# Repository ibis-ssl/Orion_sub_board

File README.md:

# Orion_sub_board
Orionのサブ基板
こちらに統合 → https://github.com/ChikuwaRobo/KiCAD_Projects.git

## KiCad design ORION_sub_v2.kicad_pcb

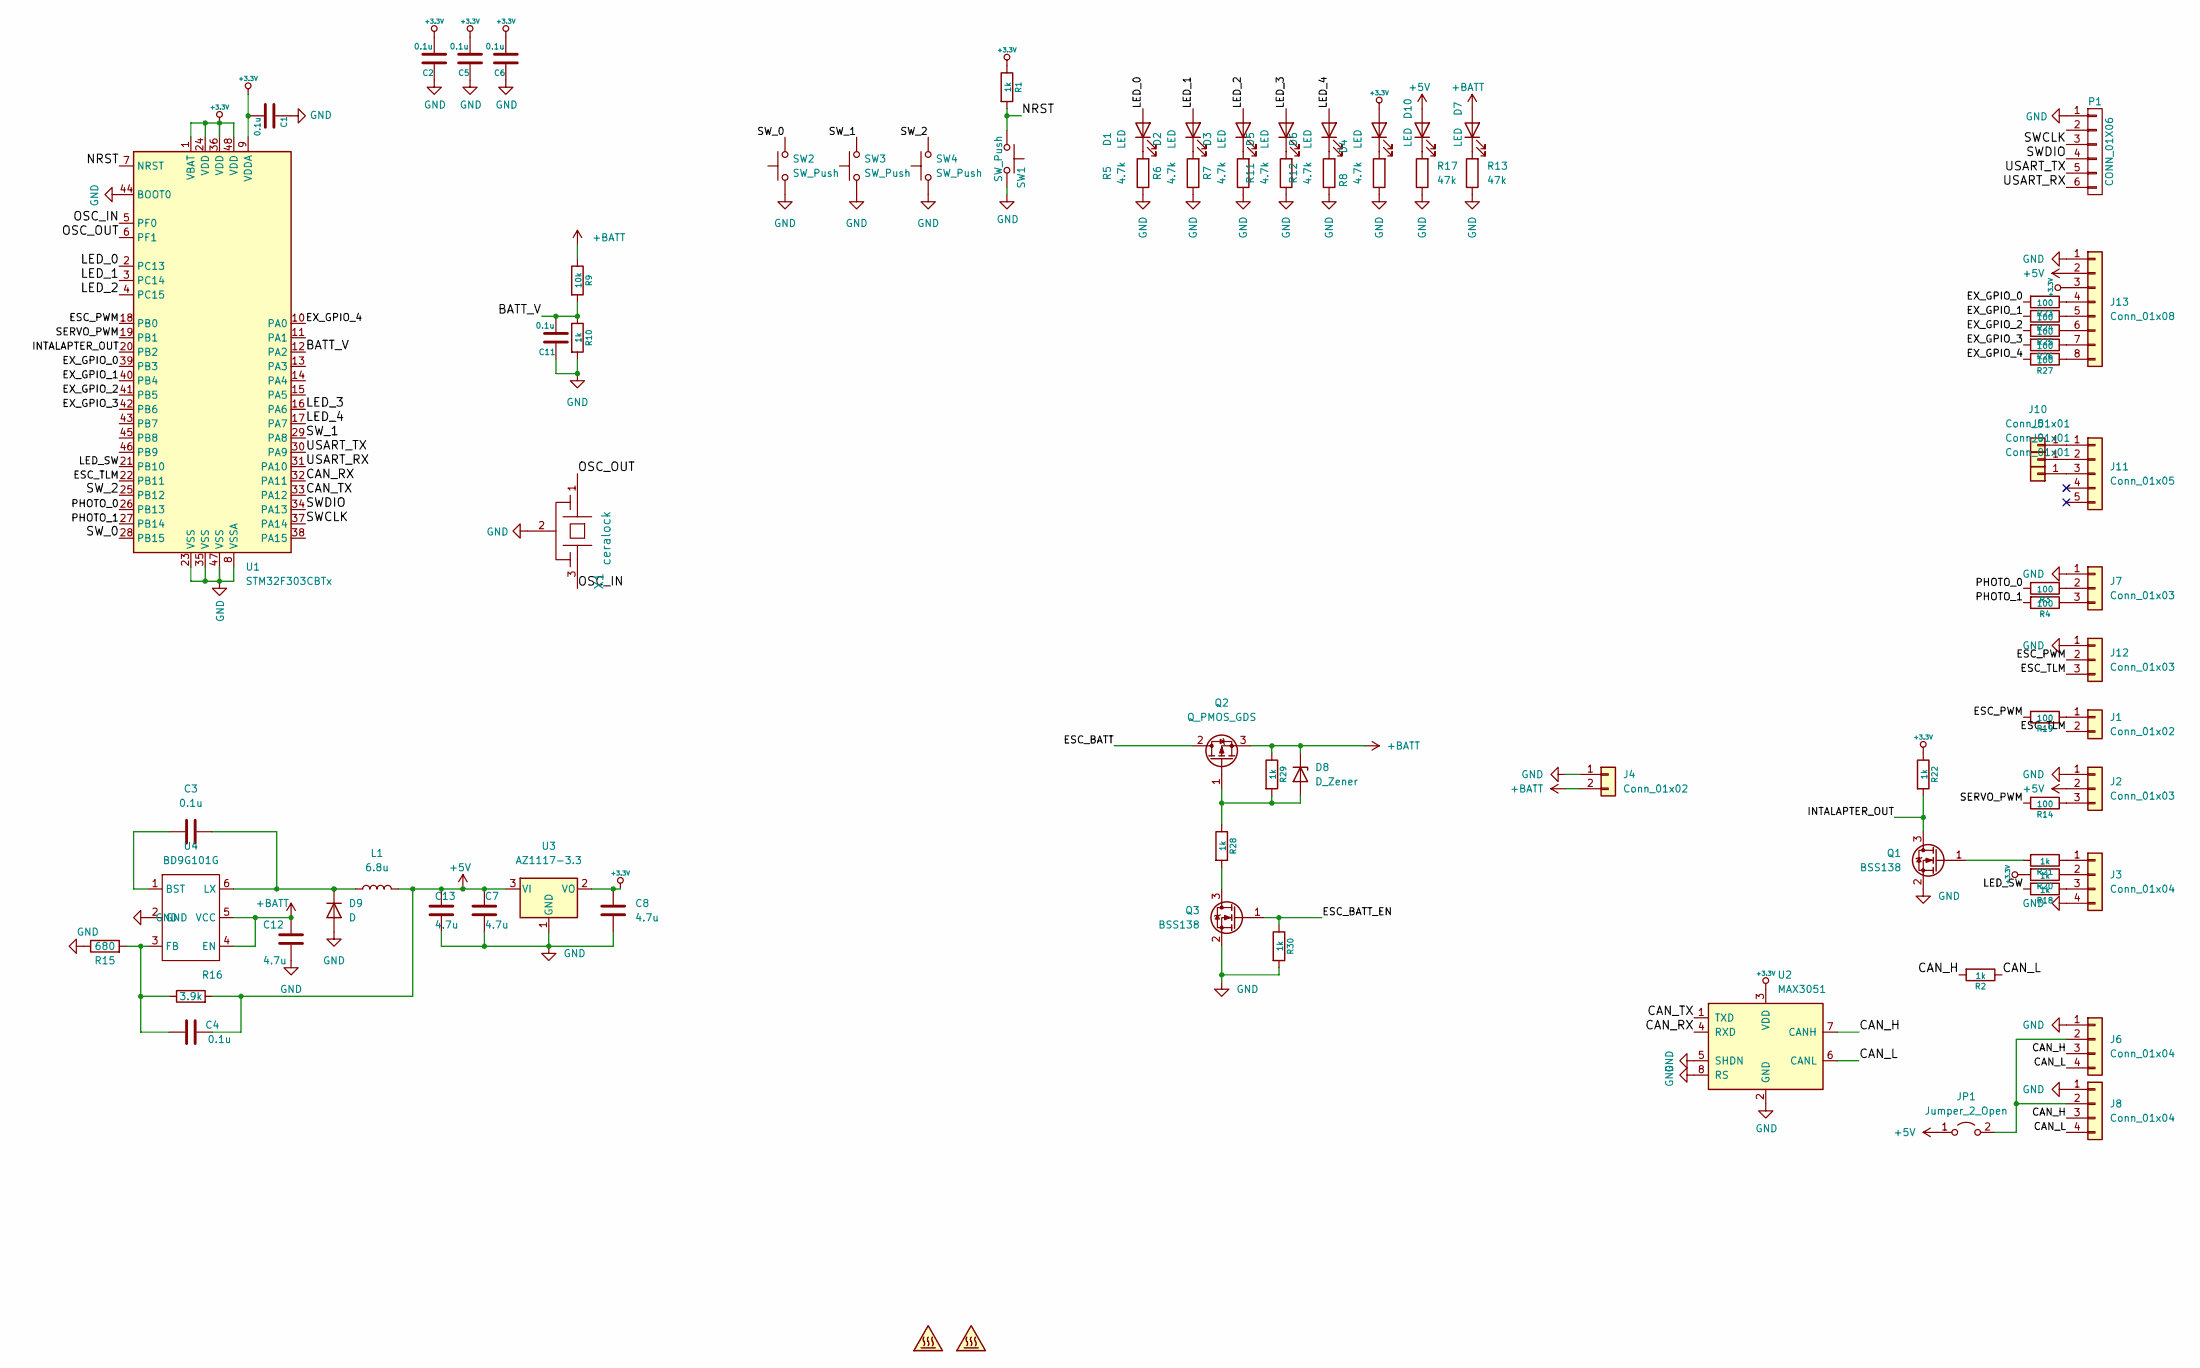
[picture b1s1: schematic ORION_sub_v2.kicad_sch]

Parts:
C1, C2, C5, C6, C11: 0.1u; C_0603_1608Metric
C3, C4: 0.1u; C_0402_1005Metric
C7, C8, C12, C13: 4.7u; C_1206_3216Metric
D1, D2, D3, D4, D5, D6, D7, D10: LED; LED_0603_1608Metric
D8: D_Zener; D_0805_2012Metric
D9: D; D_PowerDI-123
J1: Conn_01x02; Hirose_DF13-02P-1.25DSA_1x02_P1.25mm_Vertical
J2: Conn_01x03; JST_PH_S3B-PH-K_1x03_P2.00mm_Horizontal
J3, J6, J8: Conn_01x04; Hirose_DF13-04P-1.25DSA_1x04_P1.25mm_Vertical
J4: Conn_01x02; AMASS_XT30PW-M_1x02_P2.50mm_Horizontal
J5, J9, J10: Conn_01x01; WireSoldingPad_PowerTH
J7: Conn_01x03; Hirose_DF13-03P-1.25DSA_1x03_P1.25mm_Vertical
J11: Conn_01x05; 2053380003
J12: Conn_01x03; PinSocket_1x03_P2.54mm_Vertical
J13: Conn_01x08; Hirose_DF13-08P-1.25DSA_1x08_P1.25mm_Vertical
JP1: Jumper_2_Open; SolderJumper-2_P1.3mm_Open_RoundedPad1.0x1.5mm
L1: 6.8u; L_Taiyo-Yuden_NR-50xx
LG1: SYM_Hot_Small; ibis_logo_10x8mm_mask
LG2: SYM_Hot_Small; ibis_logo_10x8mm_silk
P1: CONN_01X06; ZH_B6B-ZR
Q1, Q3: BSS138; SOT-23
Q2: Q_PMOS_GDS; TO-252-2
R1, R2, R10, R18, R20, R21, R22, R28, R29, R30: 1k; R_0603_1608Metric
R3, R4, R14, R19, R23, R24, R25, R26, R27: 100; R_0603_1608Metric
R5, R6, R7, R8, R11, R12: 4.7k; R_0603_1608Metric
R9: 10k; R_0603_1608Metric
R13, R17: 47k; R_0603_1608Metric
R15: 680; R_0603_1608Metric
R16: 3.9k; R_0603_1608Metric
SW1, SW2, SW3, SW4: SW_Push; SW_Push_1P1T_NO_CK_KMR2
U1: STM32F303CBTx; LQFP-48_7x7mm_P0.5mm
U2: MAX3051; SO-8_3.9x4.9mm_P1.27mm
U3: AZ1117-3.3; SOT-23
U4: BD9G101G; SOT-23-6
X1: ceralock; Resonator_SMD_Murata_CSTxExxV-3Pin_3.0x1.1mm

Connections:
+3.3V: C1.2, C2.2, C5.2, C6.2, C8.1, D4.2 (A), J13.3, R1.1, R20.2, R22.1, U1.1 (VBAT), U1.9 (VDDA), U1.24 (VDD), U1.36 (VDD), U1.48 (VDD), U2.3 (VDD), U3.2 (VO)
+5V: C4.1, C7.1, C13.1, D10.2 (A), J2.2, J13.2, JP1.1 (A), L1.2, R16.2, U3.3 (VI)
+BATT: C12.1, D7.2 (A), D8.1 (K), J4.2, Q2.3 (S), R9.1, R29.1, U4.4 (EN), U4.5 (VCC)
/BATT_V: C11.2, R9.2, R10.1, U1.12 (PA2)
/CAN_H: J6.3, J8.3, R2.2, U2.7 (CANH)
/CAN_L: J6.4, J8.4, R2.1, U2.6 (CANL)
/CAN_RX: U1.32 (PA11), U2.4 (RXD)
/CAN_TX: U1.33 (PA12), U2.1 (TXD)
/ESC_BATT: Q2.2 (D)
/ESC_BATT_EN: Q3.1 (G), R30.1
/ESC_PWM: J12.2, R19.2, U1.18 (PB0)
/ESC_TLM: J1.2, J12.3, U1.22 (PB11)
/EX_GPIO_0: R23.2, U1.39 (PB3)
/EX_GPIO_1: R24.2, U1.40 (PB4)
/EX_GPIO_2: R25.2, U1.41 (PB5)
/EX_GPIO_3: R26.2, U1.42 (PB6)
/EX_GPIO_4: R27.2, U1.10 (PA0)
/INTALAPTER_OUT: Q1.3 (D), R22.2, U1.20 (PB2)
/LED_0: D1.2 (A), U1.2 (PC13)
/LED_1: D2.2 (A), U1.3 (PC14)
/LED_2: D3.2 (A), U1.4 (PC15)
/LED_3: D5.2 (A), U1.16 (PA6)
/LED_4: D6.2 (A), U1.17 (PA7)
/LED_SW: R18.2, U1.21 (PB10)
/NRST: R1.2, SW1.1, U1.7 (NRST)
/OSC_IN: U1.5 (PF0), X1.3
/OSC_OUT: U1.6 (PF1), X1.1
/PHOTO_0: R3.2, U1.26 (PB13)
/PHOTO_1: R4.2, U1.27 (PB14)
/SERVO_PWM: R14.2, U1.19 (PB1)
/SWCLK: P1.3, U1.37 (PA14)
/SWDIO: P1.4, U1.34 (PA13)
/SW_0: SW2.2, U1.28 (PB15)
/SW_1: SW3.2, U1.29 (PA8)
/SW_2: SW4.2, U1.25 (PB12)
/USART_RX: P1.6, U1.31 (PA10)
/USART_TX: P1.5, U1.30 (PA9)
GND: C1.1, C2.1, C5.1, C6.1, C7.2, C8.2, C11.1, C12.2, C13.2, D9.2 (A), J2.1, J3.4, J4.1, J6.1, J7.1, J8.1, J12.1, J13.1, P1.1, Q1.2 (S), Q3.2 (S), R5.1, R6.1, R7.1, R8.1, R10.2, R11.1, R12.1, R13.1, R15.1, R17.1, R30.2, SW1.2, SW2.1, SW3.1, SW4.1, U1.8 (VSSA), U1.23 (VSS), U1.35 (VSS), U1.44 (BOOT0), U1.47 (VSS), U2.2 (GND), U2.5 (SHDN), U2.8 (RS), U3.1 (GND), U4.2 (GND), X1.2
unnamed: C3.1, D9.1 (K), L1.1, U4.6 (LX)
unnamed: C3.2, U4.1 (BST)
unnamed: C4.2, R15.2, R16.1, U4.3 (FB)
unnamed: D1.1 (K), R5.2
unnamed: D2.1 (K), R6.2
unnamed: D3.1 (K), R7.2
unnamed: D4.1 (K), R8.2
unnamed: D5.1 (K), R11.2
unnamed: D6.1 (K), R12.2
unnamed: D7.1 (K), R13.2
unnamed: D8.2 (A), Q2.1 (G), R28.1, R29.2
unnamed: D10.1 (K), R17.2
unnamed: J1.1, R19.1
unnamed: J2.3, R14.1
unnamed: J3.1, R21.1
unnamed: J3.2, R20.1
unnamed: J3.3, R18.1
unnamed: J6.2, J8.2, JP1.2 (B)
unnamed: J7.2, R3.1
unnamed: J7.3, R4.1
unnamed: J10.1, J11.1
unnamed: J5.1, J11.2
unnamed: J9.1, J11.3
unnamed: J13.4, R23.1
unnamed: J13.5, R24.1
unnamed: J13.6, R25.1
unnamed: J13.7, R26.1
unnamed: J13.8, R27.1
unnamed: Q1.1 (G), R21.2
unnamed: Q3.3 (D), R28.2

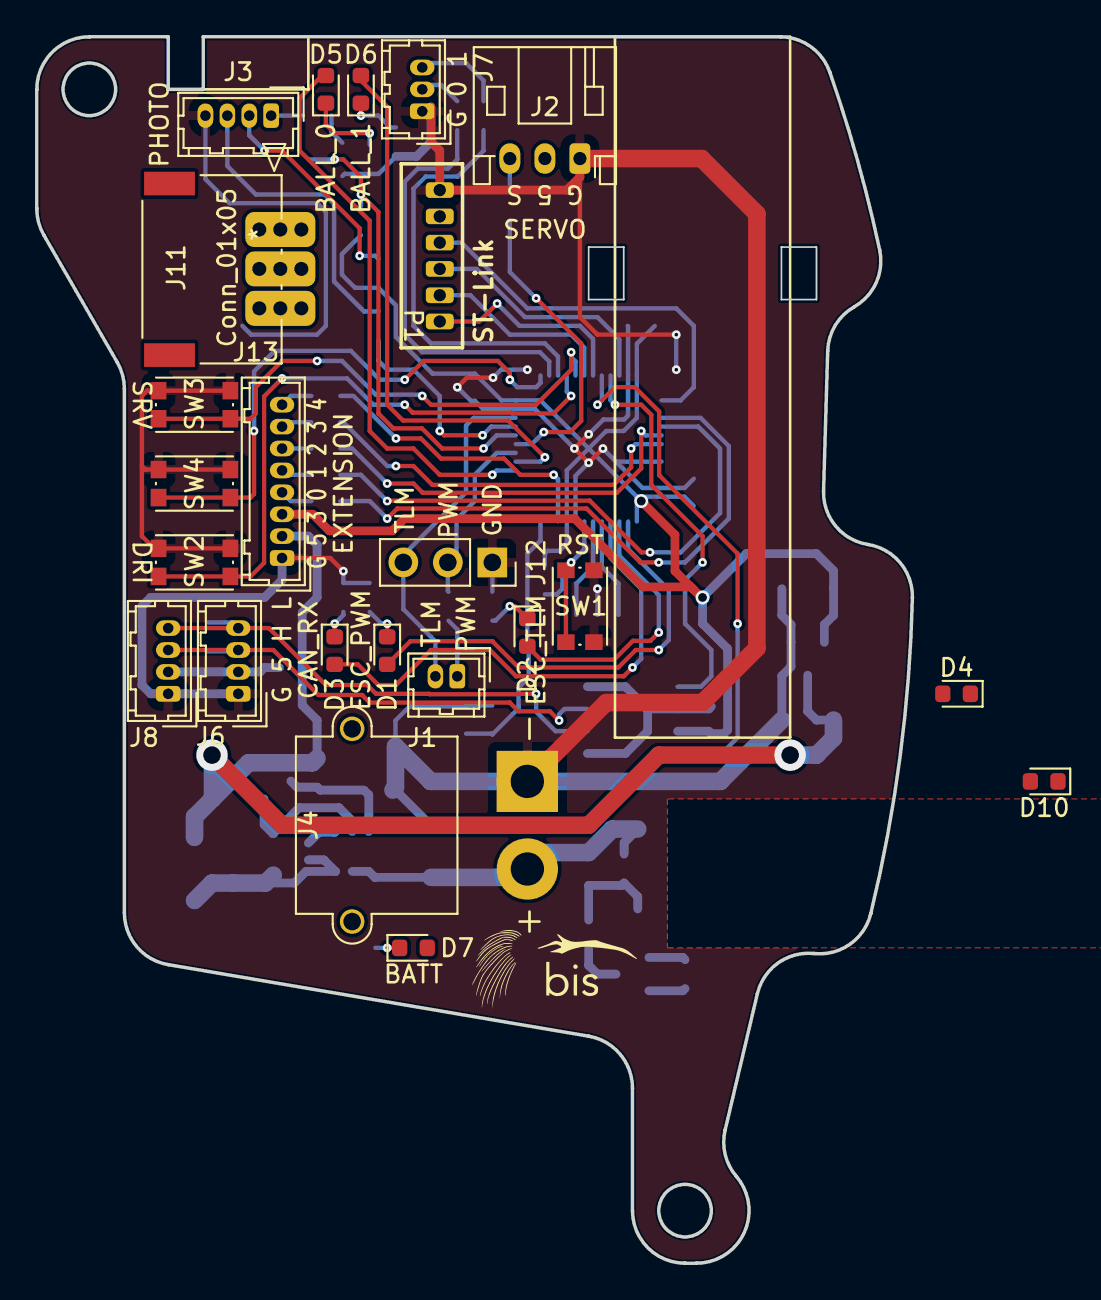
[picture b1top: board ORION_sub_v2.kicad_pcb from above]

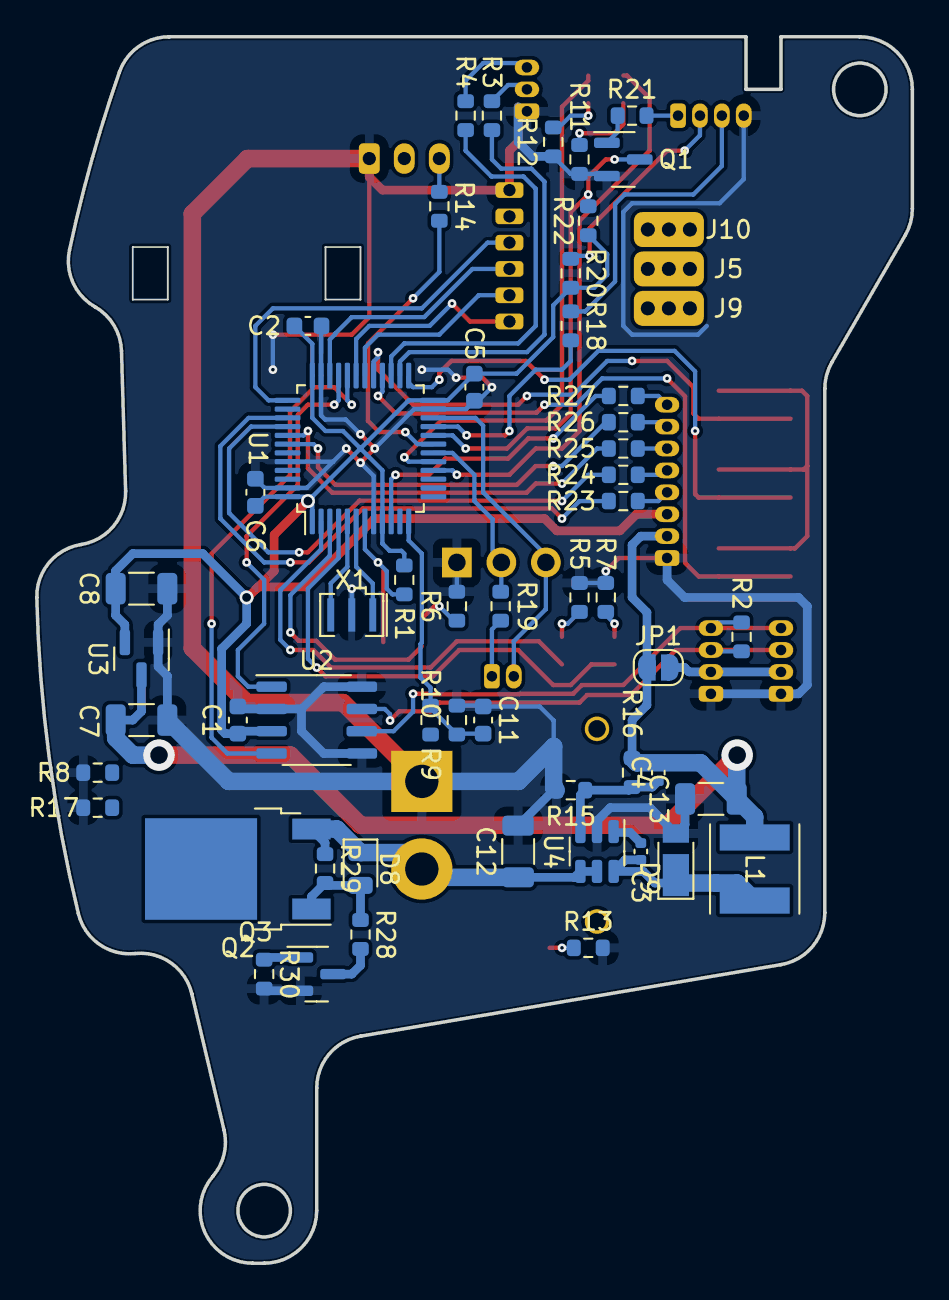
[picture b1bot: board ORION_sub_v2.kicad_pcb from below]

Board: 2 copper layers, 50.0 x 70.0 mm, 81 parts (56 on the bottom side), 67 nets.

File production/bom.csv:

Designator,Footprint,Quantity,Value,LCSC Part #
"C1, C11, C2, C5, C6",C_0603_1608Metric,5,0.1u,
"C12, C13, C7, C8",C_1206_3216Metric,4,4.7u,
"C3, C4",C_0402_1005Metric,2,0.1u,
"D1, D10, D2, D3, D4, D5, D6, D7",LED_0603_1608Metric,8,LED,
D9,D_PowerDI-123,1,D,
J1,Hirose_DF13-02P-1.25DSA_1x02_P1.25mm_Vertical,1,Conn_01x02,
"J10, J5, J9",WireSoldingPad_PowerTH,3,Conn_01x01,
J11,2053380003,1,Conn_01x05,
J12,PinHeader_1x04_P2.54mm_Vertical,1,Conn_01x04,
J2,JST_PH_S3B-PH-K_1x03_P2.00mm_Horizontal,1,Conn_01x03,
"J3, J6, J8",Hirose_DF13-04P-1.25DSA_1x04_P1.25mm_Vertical,3,Conn_01x04,
J4,AMASS_XT30PW-M_1x02_P2.50mm_Horizontal,1,Conn_01x02,
J7,Hirose_DF13-03P-1.25DSA_1x03_P1.25mm_Vertical,1,Conn_01x03,
L1,L_Taiyo-Yuden_NR-50xx,1,6.8u,
LG1,ibis_logo_10x8mm_mask,1,SYM_Hot_Small,
LG2,ibis_logo_10x8mm_silk,1,SYM_Hot_Small,
P1,ZH_B6B-ZR,1,CONN_01X06,
Q1,SOT-23,1,Q_NPN_BCE,
Q2,SOT-23,1,Q_NMOS_GSD,
Q3,TO-252-2,1,Q_NMOS_GDS,
"R1, R10, R18, R20, R21, R22, R23, R24, R25, R26",R_0603_1608Metric,10,1k,
"R11, R12, R5, R6, R7, R8",R_0603_1608Metric,6,4.7k,
"R13, R17",R_0603_1608Metric,2,47k,
"R14, R19, R3, R4",R_0603_1608Metric,4,100,
R15,R_0603_1608Metric,1,680,
R16,R_0603_1608Metric,1,3.9k,
R2,R_0603_1608Metric,1,120,
R9,R_0603_1608Metric,1,10k,
"SW1, SW2, SW3, SW4",SW_Push_1P1T_NO_CK_KMR2,4,SW_Push,
U1,LQFP-48_7x7mm_P0.5mm,1,STM32F303CBTx,
U2,SO-8_3.9x4.9mm_P1.27mm,1,MAX3051,
U3,SOT-23,1,AZ1117-3.3,
U4,SOT-23-6,1,BD9G101G,
X1,Resonator_SMD_Murata_CSTxExxV-3Pin_3.0x1.1mm,1,ceralock,

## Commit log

2023-04-16 v2 発注
2024-10-01 変更前差分
2024-10-01 スイッチ変更、電源ヒューズ追加
2024-11-02 KiCAD8.0に更新
2024-11-19 OLED追加

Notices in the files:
parts and their libraries:
Copyright 2021 Accelerated Designs. All rights reserved.
